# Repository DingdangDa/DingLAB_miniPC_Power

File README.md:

# A small, high-efficiency, elegant 19V10A DC-DC converter especially adapted for RoboMaster robots.

Based on Mornsun KJB4824SBO model.

[3D Model](https://cad.onshape.com/documents/e50259dd2ed67d63d06577b1/w/eb5fe1527c8b7bdda93aefb9/e/278cedefd56651d5bb8dcdc5?renderMode=0&uiState=65f4441e2e6a3751945f740c)

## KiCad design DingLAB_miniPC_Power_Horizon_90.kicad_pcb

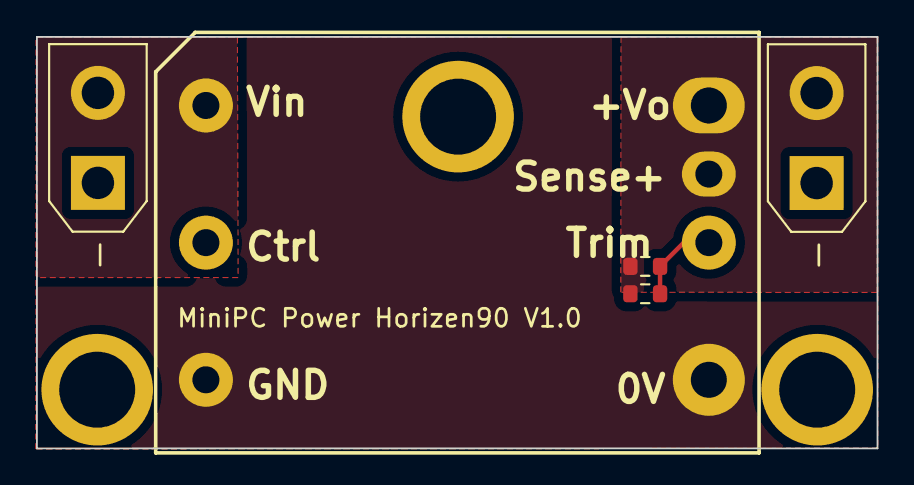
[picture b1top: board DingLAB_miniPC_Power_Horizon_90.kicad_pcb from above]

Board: 2 copper layers, 46.7 x 22.9 mm, 8 parts (1 on the bottom side), 4 nets.

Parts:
H1: MountingHole; SMTSO3020CTJ
H2, H3: MountingHole; SMTSO30110CTJ
J1: Conn_01x02_Pin; AMASS_XT30UPB-F_1x02_P5.0mm_Vertical
J2: Conn_01x02_Pin; AMASS_XT30UPB-M_1x02_P5.0mm_Vertical
R1: 150k; R_0603_1608Metric
R2: 1.15M; R_0603_1608Metric
U1: KJB48xxSBO-10A; KJB48_SBO-10A

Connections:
+24V: J2.2, U1.1 (Vin)
/Out: J1.2, R1.1, R2.1, U1.6 (Sense+), U1.7 (+Vo)
GND: J1.1, J2.1, U1.3 (GND), U1.4 (0V)
unnamed: R1.2, R2.2, U1.5 (Trim)

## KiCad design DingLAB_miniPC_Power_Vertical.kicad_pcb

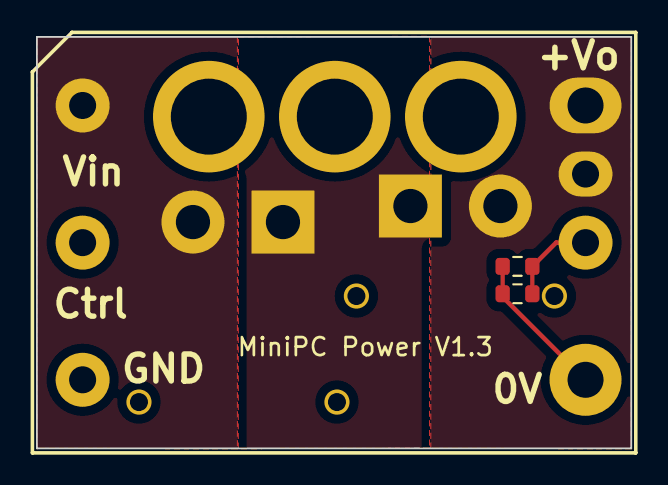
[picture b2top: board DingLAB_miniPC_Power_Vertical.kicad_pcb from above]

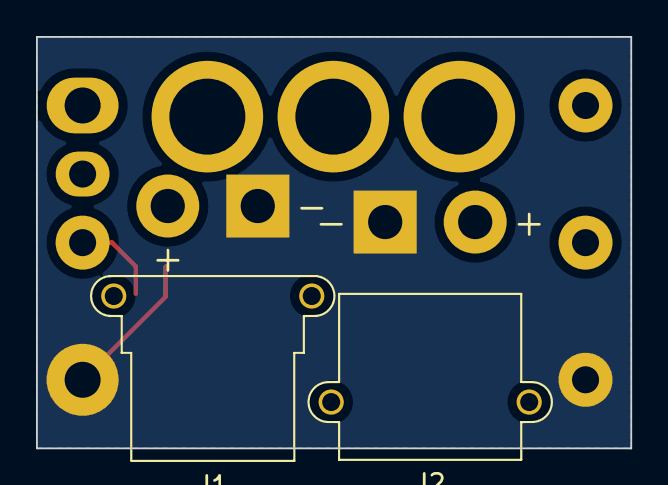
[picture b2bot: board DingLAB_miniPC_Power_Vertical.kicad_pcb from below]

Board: 2 copper layers, 33.0 x 22.9 mm, 8 parts (5 on the bottom side), 4 nets.

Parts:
H1, H2, H3: SMTSO3060CTJ
J1: Conn_01x02_Pin; AMASS_XT30PW-F_Horizontal
J2: Conn_01x02_Pin; AMASS_XT30PW-M_Horizontal
R1: 20k; R_0603_1608Metric
R2: ∞; R_0603_1608Metric
U1: KJB4815SBO-10A; KJB48_SBO-10A

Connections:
+24V: J2.2, U1.1 (Vin)
/Out: J1.2, U1.6 (Sense+), U1.7 (+Vo)
GND: J1.1, J2.1, R1.2, R2.1, U1.3 (GND), U1.4 (0V)
unnamed: R1.1, R2.2, U1.5 (Trim)

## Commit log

2024-03-18 Update Vertical and product
2024-03-26 Fix bug
